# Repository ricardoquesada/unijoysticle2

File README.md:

# Unijoysticle™ 2

![logo][uni_logo]

Unijoysticle is a device that allows you to use modern Bluetooth gamepads and mice in retro computers.

Unijoysticle 2 models:

|                                          | 800XL                       | C64                         | A500                        | 2+                                 | 2                                     |
| ---------------------------------------- | --------------------------- | --------------------------- | --------------------------- | ---------------------------------- | ------------------------------------- |
| Top                                      | ![uni2800xl_photo_front]    | ![uni2c64_photo_front]      | ![uni2a500_photo_front]     | ![uni2plus_photo_front]            | ![uni2_photo_front]                   |
| Bottom                                   | ![uni2800xl_photo_back]     | ![uni2c64_photo_back]       | ![uni2a500_photo_back]      | ![uni2plus_photo_back]             | ![uni2_photo_back]                    |
| Release date                             | July 2023                   | March 2023                  | July 2022                   | October 2021                       | April 2019                            |
| Best for                                 | Atari 800XL / 600XL         | C64 / C128                  | Amiga                       | -                                  | -                                     |
| Good for                                 | Atari 400 / Amiga / AtariST | Amiga / AtariST             | C64 / AtariST / Atari 8bit  | C64 / Amiga / AtariST / Atari 8bit | C64 / Amiga / AtariST / Atari 8bit    |
| Status                                   | Active / Supported          | Active / Supported          | Active / Supported          | Discontinued / Supported           | Discontinued / Supported              |
| Amiga / AtariST mouse support            | Yes                         | No                          | Yes                         | Yes                                | Yes                                   |
| Amiga / AtariST 2nd & 3rd button support | No                          | No                          | Yes                         | Yes                                | Only in Port 1                        |
| Atari 8-bit 2nd & 3rd button support (5) | Yes                         | No                          | No                          | No                                 | No                                    |
| C64 2nd & 3rd button support             | No                          | Yes                         | No                          | No                                 | No                                    |
| C64 4th and 5th button support (4)       | No                          | Yes                         | No                          | No                                 | No                                    |
| C64 Paddle support                       | No                          | Might (1)                   | No                          | No                                 | No                                    |
| Rumble (2)                               | No                          | Yes                         | No                          | No                                 | No                                    |
| Fits                                     | 800XL / 600XL               | C64 / C128                  | Amiga 500 / 1200            | C64 / C128                         | C64 / C128                            |
| Buttons                                  | Reset, Mode, Swap           | Reset, Mode, Swap           | Reset, Mode,  Swap          | Reset, Mode                        | Reset, Mode                           |
| LEDs                                     | Port 1, 2, Bluetooth, Power | Port 1, 2, Bluetooth, Power | Port 1, 2, Bluetooth, Power | Port 1, 2, Power                   | Port 1, 2, Power                      |
| Filter noise ([Issue #17][issue_17])     | Yes                         | Yes                         | Yes                         | Yes                                | No                                    |
| Case friendly                            | Yes                         | Yes                         | Yes                         | Yes                                | No                                    |
| Easy to solder                           | No. Most components are SMD | No. Most components are SMD | No. Most components are SMD | No. Most components are SMD        | Yes. All components are through-hole  |
| Self-powered                             | Yes                         | Yes                         | Yes                         | Yes                                | Yes, can be turned on/off with switch |
| External power                           | USB                         | USB                         | USB                         | USB                                | Both USB and Barrel Jack 5V+          |
| Total Size (mm)                          | 65 x 75 x 13.6              | 72 x 68 x 13.6              | 67 x 72 x 13.6              | 64 x 64 x 13.6                     | 63 x 66 x 17                          |
| PCB Size (mm)                            | 53 x 72 x 1.6               | 63 x 60 x 1.6               | 52 x 67 x 1.6               | 49 x 62 x 1.6                      | 46 x 57 x 1.6                         |
| Weight (gr)                              | 27                          | 27.1                        | 25.6                        | 24                                 | 37                                    |
| Current (mA)                             | ~96                         | ~96                         | ~96                         | ~96                                | ~100                                  |
| USB connector                            | Micro USB                   | Micro USB                   | Micro USB                   | Micro USB                          | Micro USB                             |

Notes:

- (1): Hardware physically connected, but firmware is still WIP.
- (2): Some C64 games can turn on/off rumble on gamepads. See: [Rambo], and [Lemans] ([video][rumble_video])
- (3): Right and Middle mouse buttons not supported in C64.
- (4): Based on [CrystalCT 5 buttons joystick][crystalct/5plusbuttonsJoystick] ([video][5_buttons_video])
- (5): Based on [Ascrnet Joy 2B+][atari_joy2bplus]

Unijoysticle 2 allows you to use modern Bluetooth gamepads. E.g. DualSense controller in retro computers like the Commodore 64, Amiga and AtariST.

It also supports mice (for Amiga / AtariST only).

[issue_17]: https://gitlab.com/ricardoquesada/unijoysticle2/-/issues/17
[uni2_photo_front]: https://lh3.googleusercontent.com/pw/AM-JKLUphquTBg9JoV-L7wuMtze_aKIJ8LvfokTakuBKSVFClziLWCViggcrlNZtqGUMgv6u6yYpZ_RuE2jdGSn3Q0oYl0jOQzzGcutRt-JiMjLZY_oAvK4LehrawNj_aNbthCJ-VEJzsW3dywhJNekjhTsfNQ=-no
[uni2_photo_back]: https://lh3.googleusercontent.com/pw/AM-JKLXnMbJt7A55lUrtmiuKj4As98He7ZVi6YuPKg8N1sGbw1w5d5TtC8B-ilfoqC5QCKcZG8MFkmHNj5HgVbP8fdHhMBPx2CLgyRhaRmohx0SWF-_wZ57WYCfo7RlH4k7sEmh1txsTvHto2ko0H_0l9aUALg=-no
[uni2plus_photo_front]: https://lh3.googleusercontent.com/pw/AM-JKLWV2Zo912VtOfuM71AluanNXGwVQiAehNEiQ1VL3L7SkWDl-9k0fA6tfza9QpGL52petBfFFFHMb8rh_ybSj17LOQA70IycMDQw6AVqlN8Jp4HDWT8sWcXHIPEQZTxNuQ-RFygKbmVpW2n52wwi5cJgwA=-no
[uni2plus_photo_back]: https://lh3.googleusercontent.com/pw/AM-JKLWs_G63eJRX8WuVVRoKKur8UQ-VcWTNbmkjFumwZYvDRhgjqamVa-X9CROAnoPyK3sHDmfwtqAtJiI1DHiwlINBPCgiEY4yWFYWl8SlHA_QOG7LmVKuOKy1UQa-5dALC2r0FBfhS9He6utE7Kz5nWAXiw=-no
[uni2a500_photo_front]: https://lh3.googleusercontent.com/pw/AM-JKLU1BbKnbuLE7Oa_VOY3AnBjYwNVcAPKJcmYa7WUnCK5gMM1bHZyK3lTZ1Mo0NtS30ogeeSqxySx3Qi2ux3AGOlocQnQe9a87NoiKz5tnmHV_IGf3hPln0qsr8t5yfD5biKKVbGlRJ6vN2IbmI8H2Wg6iw=-no
[uni2a500_photo_back]: https://lh3.googleusercontent.com/pw/AM-JKLXMUngI6ctahY5clP-76UBjUem9L4Eehj4GFsEwUJwtZ3-MuZCV2nOsxiN3Go1PKvoc9sJbLRY8hCZ9TcV4cq5AtcAtscdjH1LiNzltFSgQY4IQEwSiPHfvhjhZCDezhgHKQDrmmA3EGFM7kJ4MKNxtig=-no
[bluepad32-fw]: https://gitlab.com/ricardoquesada/bluepad32
[uni2c64_photo_front]: https://lh3.googleusercontent.com/pw/AMWts8AzoDnIOIiM-50UpjAqY8OgdsM6pzM3BuYWb2ZOg4K_o4TxygtSjuZvrKI92lrl4Qqf8sLT6PtLYsXzDbragTDgoeX4yTpymqoc450FiyjiBT1YHxRbLBtGWgUOQHezXUxKCORs5aOcxPwowfrgR4PcQw=-no
[uni2c64_photo_back]: https://lh3.googleusercontent.com/pw/AMWts8C_vxauz3FAOv8NGAh64LGTExHwCj0N0bX73xsWIeDyR3efFPPUQb3JJQK5S8Qcm9B8bx3r_yio6WWAML1si4u8E9FejXP9DL8vxSCg_TR7rLi5aPiwisQaIptN8hJdfz3Zoh_B4cqiRE9vMi9t50R_gw=-no
[uni2800xl_photo_front]: https://lh3.googleusercontent.com/pw/AIL4fc9fcgdY3Gka6iSZmyUlBTA1Q9ABujo-9v_4qE85St2GdW-2TBzzLNx-pc25o0rFloL0ghWZDDVW_kGWpQjcXaP-SJf9NWPnNw-2jpc_8tcVKp8gzLH7fxnFd7DBEV1ahWYLy97WvthAy7p193wtZ7uM4w=-no
[uni2800xl_photo_back]: https://lh3.googleusercontent.com/pw/AIL4fc9PNSKKiA7PHsUTLKXGF1O9ywK-qLHS0nw2-Y6FxWQcgmtZJjajQh9Uch0aqZ2Pw-grH_Vg05IKYZilissF6nxUJPDszew0ouzGu91golm1RYJJpPS0CDANAfk3_O4qbwN_gam6dgGnafzsk4u0Xke0uw=-no
[Rambo]: https://gitlab.com/ricardoquesada/c64-rambo
[Lemans]: https://gitlab.com/ricardoquesada/c64-lemans
[crystalct/5plusbuttonsJoystick]: https://github.com/crystalct/5plusbuttonsJoystick/
[5_buttons_video]: https://www.youtube.com/watch?v=9Em_kUAHEuA
[rumble_video]: https://www.youtube.com/watch?v=vCj45OX43JE
[atari_joy2bplus]: https://github.com/ascrnet/Joy2Bplus
[uni_logo]: https://lh3.googleusercontent.com/pw/AIL4fc_k4CtBs9deXjMuCJOotXbNoRwON1CdYCMshG41PpEf2v-7xc2IcIPFvYCOFeLriESlXEJhm5nK72st8v1E04ZzyqawW8x5DPJt2ug6ZzhGXdnJvasD577CX1YbHRWDtmlz1JtyhDNHE_BeBeNnVb92vg=-w200-no?authuser=0

## Basic functionality

One Bluetooth gamepad controls one joystick.
You need two gamepads to control the two joysticks.

The mappings are:

- D-pad/joypad: controls up/down/left/right.
- Button A / Cross: fire button
- Button B / Circle: "up"  (ideal for platform games).
- Button X / Square: 2nd button (Amiga / AtariST only)
- Button Y / Triangle: 3rd button (Amiga / AtariST only)
- Button shoulder-right: autofire.
- System button swaps between Joystick 1 and 2

## Twin Stick functionality (AKA Enhanced mode)

When in "Enhanced mode", you control the two joysticks with only one gamepad.
The mappings are:

- Left joypad / d-pad: control Joystick 2 movements.
- Right joypad: control Joystick 1 movements.
- Button A / Cross: fire for Joystick 2
- Button B / Circle: fire for Joystick 1
- Button X / Square: 2nd button for Joystick 2
- Button Y / Triangle: 2nd button for Joystick 1
- Button Shoulder Left: auto-fire for Joystick 2
- Button Shoulder Right: auto-fire for Joystick 1

This mode is ideal for games like [Commando][2] or [1942][3] since it allows you
throw grenades / roll by pressing Button B.

## Supported controllers

### Gamepads

- Sony DualSense
- Sony DUALSHOCK 4
- Sony DUALSHOCK 3
- Nintendo Switch Pro
- Nintendo JoyCons
- Nintendo Wii U
- Nintendo Wii + accesories
- Xbox Wireless controller (model 1708)
- Steam
- Stadia
- Android gamepads
- PC/Windows gamepads
- 8BitDo controllers
- iCade
- And more

See:

* [Supported gamepads][gamepads]
* [Supported mice][mice]

[gamepads]: https://gitlab.com/ricardoquesada/unijoysticle2/blob/master/docs/supported_gamepads.md
[mice]: https://gitlab.com/ricardoquesada/bluepad32/blob/develop/docs/supported_mice.md

### Mice

Mouse emulation is only available for **Amiga and Atari ST** computers.

For a detailed list of supported mice, see here:

* [Supported mice][supported_mice]

[supported_mice]:  https://gitlab.com/ricardoquesada/bluepad32/blob/develop/docs/supported_mice.md

## Order info

If you are looking for ready-to-use boards, you can purchase one from here:

Looking for a remix and/or 3rd party vendors. Go here: [SELLING_DEVICES.md][selling_devices]

[selling_devices]: SELLING_DEVICES.md

## More Info

- [Users guide][users_guide]
- [Discord][discord]
- [Email group][email_group]

[users_guide]: https://gitlab.com/ricardoquesada/unijoysticle2/blob/master/docs/user_guide.md
[discord]: https://discord.gg/r5aMn6Cw5q
[email_group]: https://groups.google.com/forum/#!forum/unijoysticle

[1]: https://retro.moe/unijoysticle
[2]: https://csdb.dk/release/?id=137173
[3]: https://csdb.dk/release/?id=38140

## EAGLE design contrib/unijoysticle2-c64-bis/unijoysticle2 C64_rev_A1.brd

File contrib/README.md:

Contributions by the community.

Kopsec C64:
 - c64/ Unijoysticle 2 - REV E / REV H
 - c64/ Unijoysticle 2 - Rev A1, based on new Unijoysticle C64 model

Eduardo Casino:
 - C16/Plus4 board

Hyvax:
  - NeoGeo board

Aakko:
  - Case for Unijosyticle 2+

Goblin Hero:
  - Case for Unijoysticle 2 A500

Albert Herranz:
  - MSX boards
    * [msx-joyblue-v1](https://github.com/herraa1/msx-joyblue-v1)
    * [msx-joyblue-v2](https://github.com/herraa1/msx-joyblue-v2)

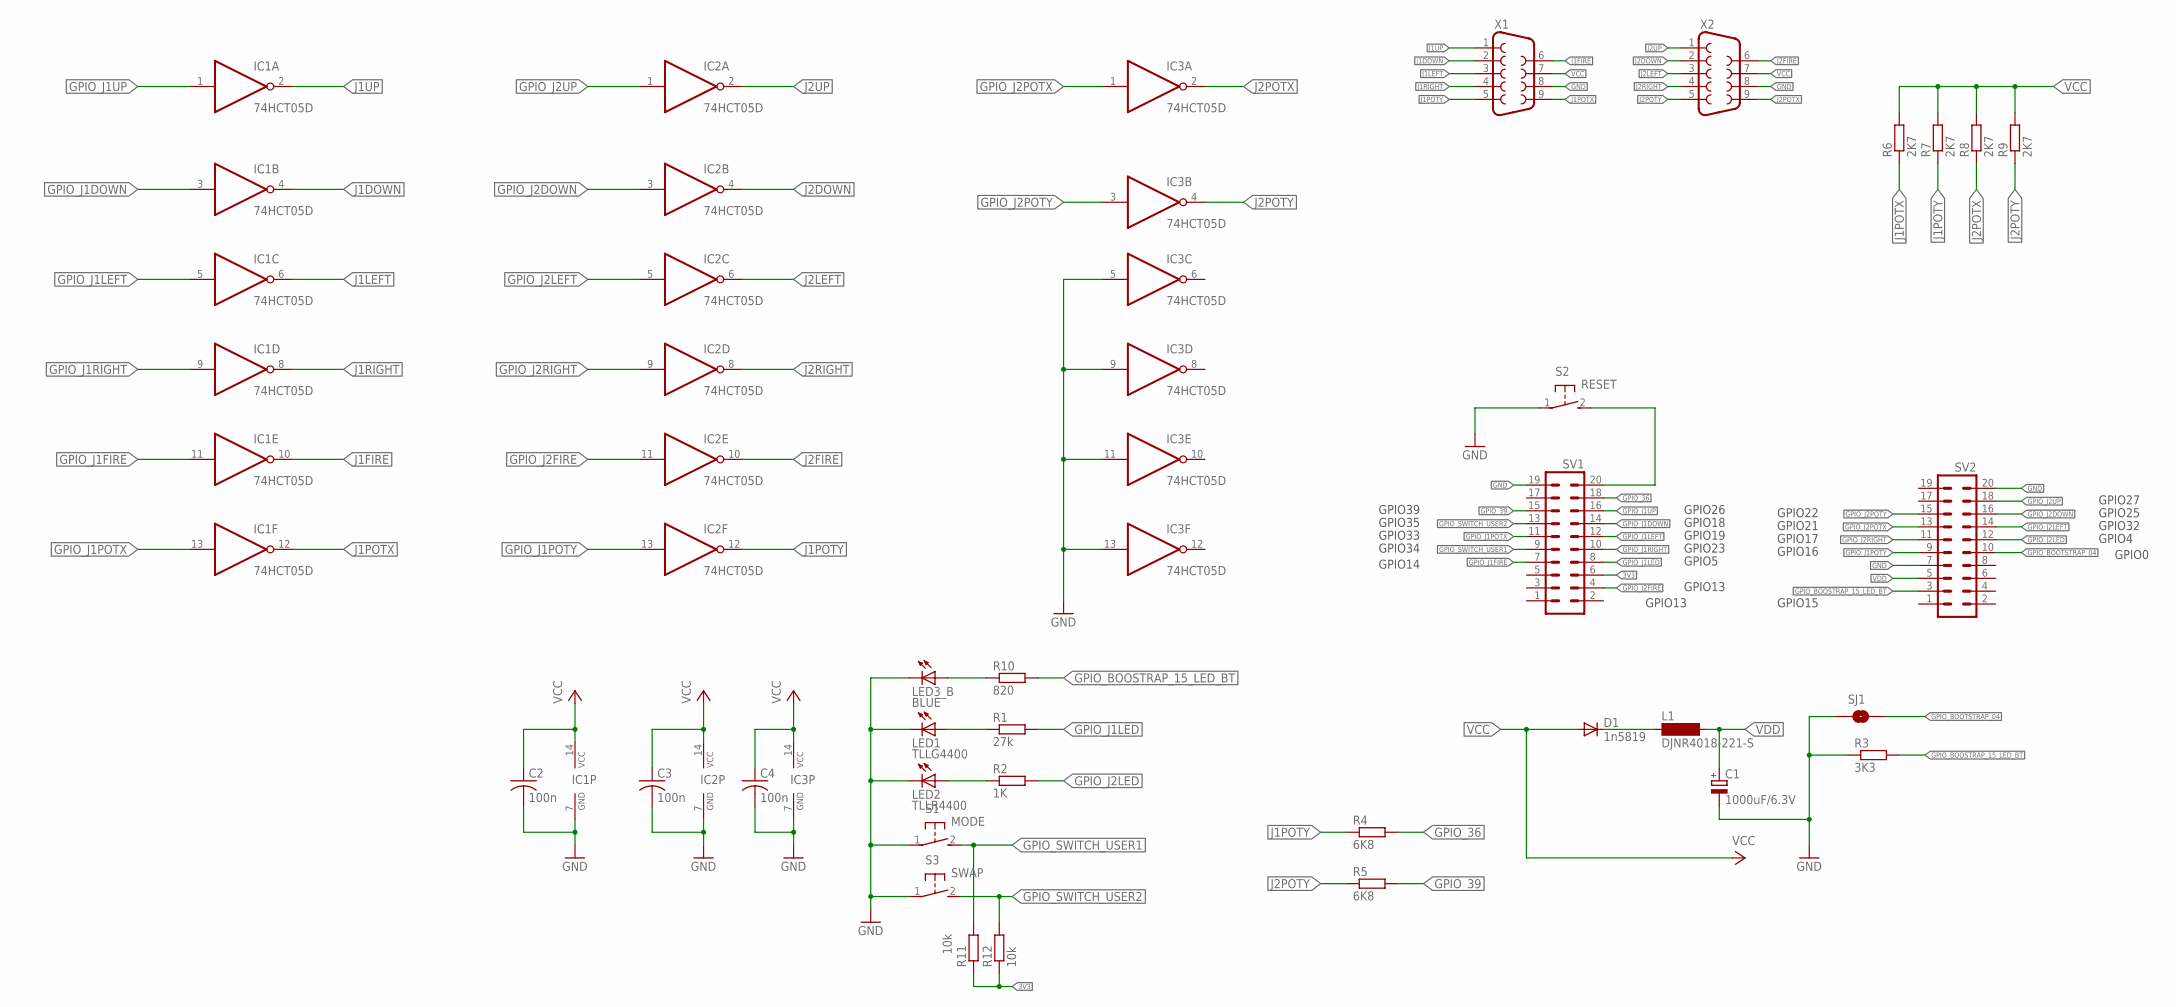
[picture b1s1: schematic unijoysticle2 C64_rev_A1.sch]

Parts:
C1: 1000uF/6.3V; 140CLH-1010
C2, C3, C4: 100n; C0805K
D1: 1n5819; DO214AC
IC1, IC2, IC3: 74HCT05D; SO14
L1: DJNR4018-221-S; SM-NE45
LED1: TLLG4400; LED3MM
LED2: TLLR4400; LED3MM
LED3_B: BLUE; LED3MM
R1: 27k; M0805
R2: 1K; M0805
R3: 3K3; M0805
R4, R5: 6K8; M0805
R6, R7, R8, R9: 2K7; M0805
R10: 820; M0805
R11, R12: 10k; M0805
S1: MODE; B3F-31XX
S2: RESET; B3F-31XX
S3: SWAP; B3F-31XX
SJ1: SOLDERJUMPERTRACE; SJ_2S-TRACE
SV1, SV2: MA10-2
X1, X2: DB9

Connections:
3V3: R11.1, R12.1, SV1.6
GND: C1.-, C2.2, C3.2, C4.2, IC1.7 (GND), IC2.7 (GND), IC3.5 (I), IC3.7 (GND), IC3.9 (I), IC3.11 (I), IC3.13 (I), LED1.K (C), LED2.K (C), LED3_B.K (C), R3.1, S1.1, S2.1, S3.1, SJ1.1, SV1.19, SV2.7, SV2.20, X1.8, X2.8
GPIO_36: R4.2, SV1.18
GPIO_39: R5.2, SV1.15
GPIO_BOOSTRAP_15_LED_BT: R3.2, R10.2, SV2.3
GPIO_BOOTSTRAP_04: SJ1.2, SV2.10
GPIO_J1DOWN: IC1.3 (I), SV1.14
GPIO_J1FIRE: IC1.11 (I), SV1.7
GPIO_J1LED: R1.2, SV1.8
GPIO_J1LEFT: IC1.5 (I), SV1.12
GPIO_J1POTX: IC1.13 (I), SV1.11
GPIO_J1POTY: IC2.13 (I), SV2.9
GPIO_J1RIGHT: IC1.9 (I), SV1.10
GPIO_J1UP: IC1.1 (I), SV1.16
GPIO_J2DOWN: IC2.3 (I), SV2.16
GPIO_J2FIRE: IC2.11 (I), SV1.4
GPIO_J2LED: R2.2, SV2.12
GPIO_J2LEFT: IC2.5 (I), SV2.14
GPIO_J2POTX: IC3.1 (I), SV2.13
GPIO_J2POTY: IC3.3 (I), SV2.15
GPIO_J2RIGHT: IC2.9 (I), SV2.11
GPIO_J2UP: IC2.1 (I), SV2.18
GPIO_SWITCH_USER1: R11.2, S1.2 (S), SV1.9
GPIO_SWITCH_USER2: R12.2, S3.2 (S), SV1.13
J1DOWN: IC1.4 (O), X1.2
J1FIRE: IC1.10 (O), X1.6
J1LEFT: IC1.6 (O), X1.3
J1POTX: IC1.12 (O), R6.1, X1.9
J1POTY: IC2.12 (O), R4.1, R7.1, X1.5
J1RIGHT: IC1.8 (O), X1.4
J1UP: IC1.2 (O), X1.1
J2DOWN: IC2.4 (O), X2.2
J2FIRE: IC2.10 (O), X2.6
J2LEFT: IC2.6 (O), X2.3
J2POTX: IC3.2 (O), R8.1, X2.9
J2POTY: IC3.4 (O), R5.1, R9.1, X2.5
J2RIGHT: IC2.8 (O), X2.4
J2UP: IC2.2 (O), X2.1
unnamed: LED1.A, R1.1
unnamed: LED2.A, R2.1
unnamed: S2.2 (S), SV1.20
unnamed: LED3_B.A, R10.1
unnamed: D1.C, L1.1
VCC: C2.1, C3.1, C4.1, D1.A, IC1.14 (VCC), IC2.14 (VCC), IC3.14 (VCC), R6.2, R7.2, R8.2, R9.2, X1.7, X2.7
VDD: C1.+, L1.2, SV2.5

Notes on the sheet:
GPIO35
GPIO33
GPIO34
GPIO14
GPIO39
GPIO26
GPIO18
GPIO19
GPIO23
GPIO5
GPIO13
GPIO27
GPIO25
GPIO32
GPIO4
GPIO0
GPIO22
GPIO21
GPIO17
GPIO16
GPIO15

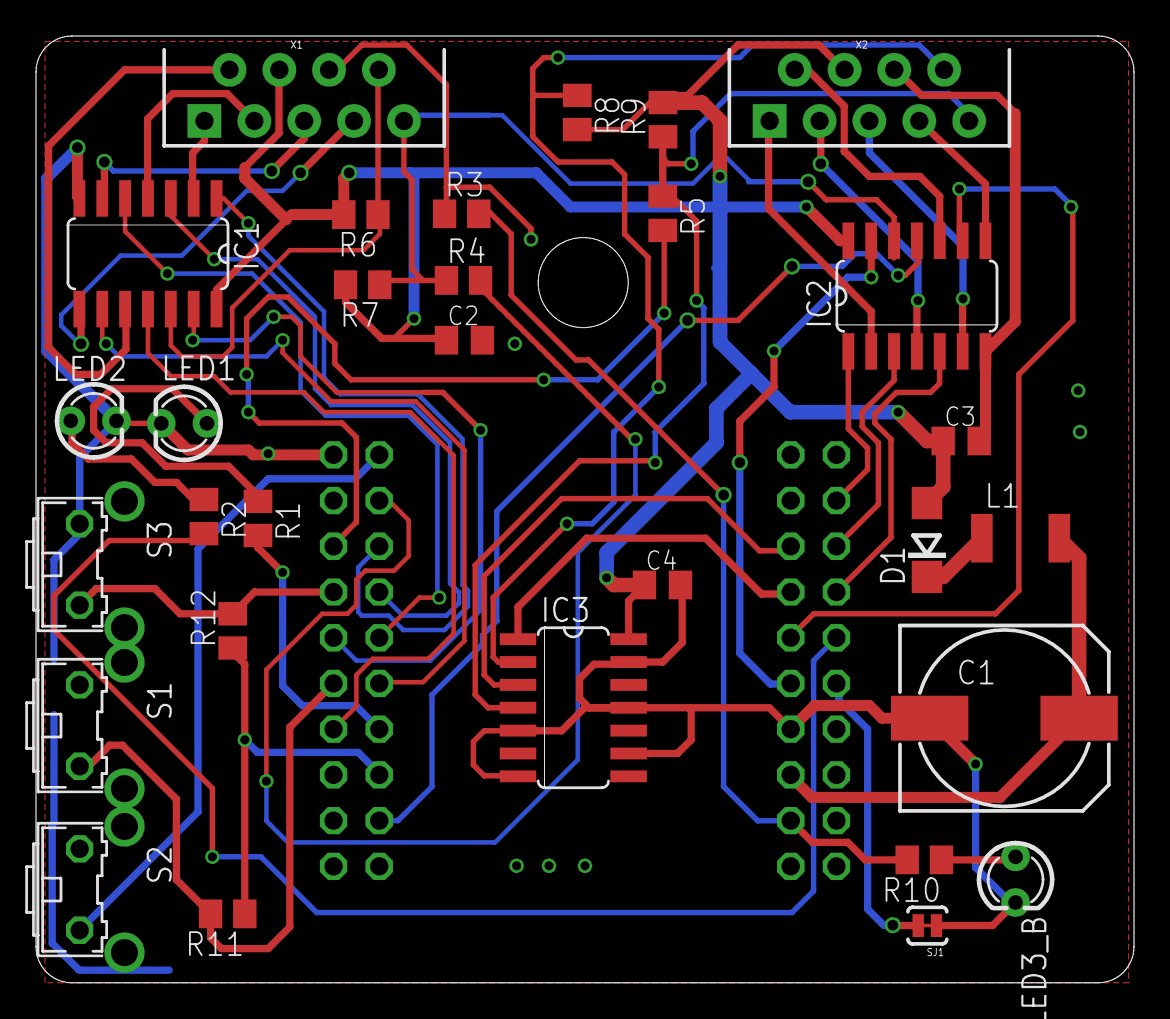
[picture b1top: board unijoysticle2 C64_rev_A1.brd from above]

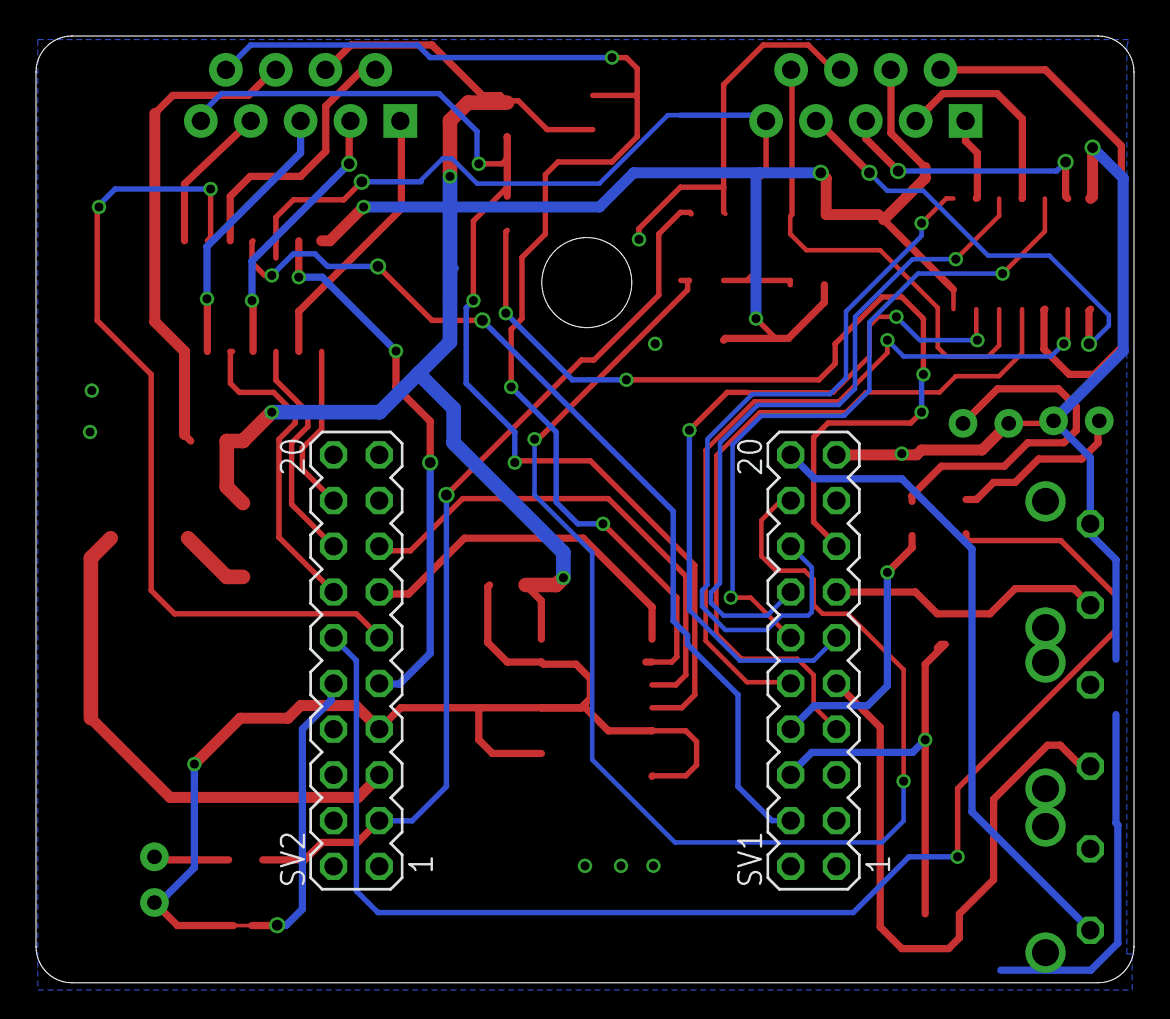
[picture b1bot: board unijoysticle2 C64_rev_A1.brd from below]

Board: 2 copper layers, 61.0 x 52.6 mm, 32 parts (2 on the bottom side), 45 nets.

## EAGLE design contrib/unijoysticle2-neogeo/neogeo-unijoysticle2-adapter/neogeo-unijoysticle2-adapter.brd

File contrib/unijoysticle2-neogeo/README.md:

# Unijoysticle2 for NeoGeo

## Projects

### Unijoysticle2 for NeoGeo

Includes PCB & schematic (Eagle CAD 6.5.0): Unijoysticle2 NeoGeo version - with DB15 connector.

### Unijoysticle2 Adapter for NeoGeo

Includes PCB & schematic (Eagle CAD 6.5.0): Adapter for Unijoysticle2 - 2x DB9 -> DB15

## NeoGeo pinout

- NeoGeo DB15 pinout reference
- C64 control port pinout reference
- table describing how corresponding pins are connected
- gamepad button mappings, NeoGeo and MVS controller for reference

## Mappings

Replace file `uni_joystick.c` in in Bluepad32 source code and compile it using `unijoysticle` as `PLATFORM`.

## Additional notes

- neogeo-unijoysticle2 is supposed to be ONLY used as self powered - do not plug in usb power simultaneously, there are no protection diodes (add em if You wish)
- before exporting to gerber all traces on board files should be further optimized, can be traced better/prettier
- description layers should be cleaned up and aligned
- board dimensions should be further adjusted
- uni_joystick.c is still from the version before "enhanced mode bug fix" so J2 = J1
- ment to be used in enhanced mode only, of course, due to 10 controller inputs are required - there is no point in using it in basic mode
- tested 11.12.2021 and working fine with NeoGeo MVS MV1A - should of course work as well with other MVS boards and AES
- keep in mind some MVS supergun's may have DB15 connectors upside down - mirror DB15 connector on the adapter or standalone pcb before making gerbers, otherwise (due to esp32 sticking up out of the pcb) there may be issues plugging in adapter or standalone pcb to Your MVS or AES
- solder cup DB15/DB9 connector or THT connectors may be used - alter board files according to Your preferences

## Author

Hyvax

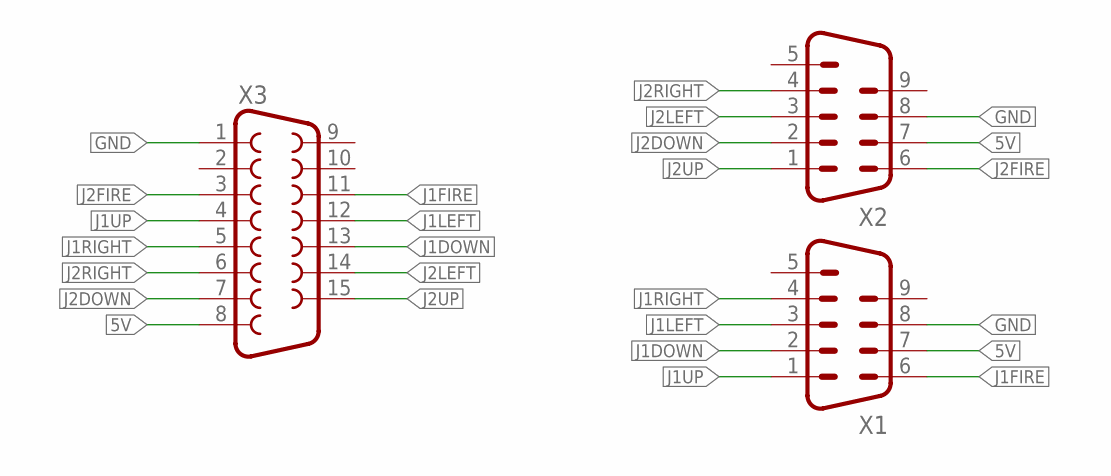
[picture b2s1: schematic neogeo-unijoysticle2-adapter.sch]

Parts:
X1, X2: M09D
X3: F15D

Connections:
5V: X1.7, X2.7, X3.8
GND: X1.8, X2.8, X3.1
J1DOWN: X1.2, X3.13
J1FIRE: X1.6, X3.11
J1LEFT: X1.3, X3.12
J1RIGHT: X1.4, X3.5
J1UP: X1.1, X3.4
J2DOWN: X2.2, X3.7
J2FIRE: X2.6, X3.3
J2LEFT: X2.3, X3.14
J2RIGHT: X2.4, X3.6
J2UP: X2.1, X3.15

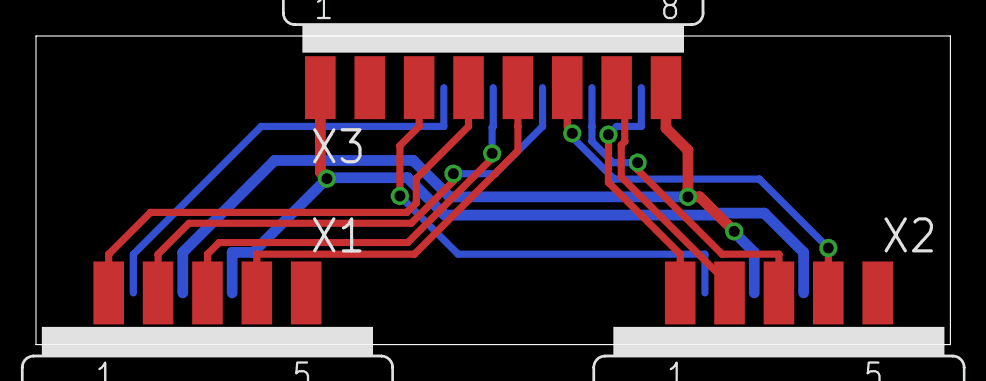
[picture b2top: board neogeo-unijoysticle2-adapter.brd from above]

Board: 2 copper layers, 50.8 x 17.1 mm, 3 parts (0 on the bottom side), 12 nets.

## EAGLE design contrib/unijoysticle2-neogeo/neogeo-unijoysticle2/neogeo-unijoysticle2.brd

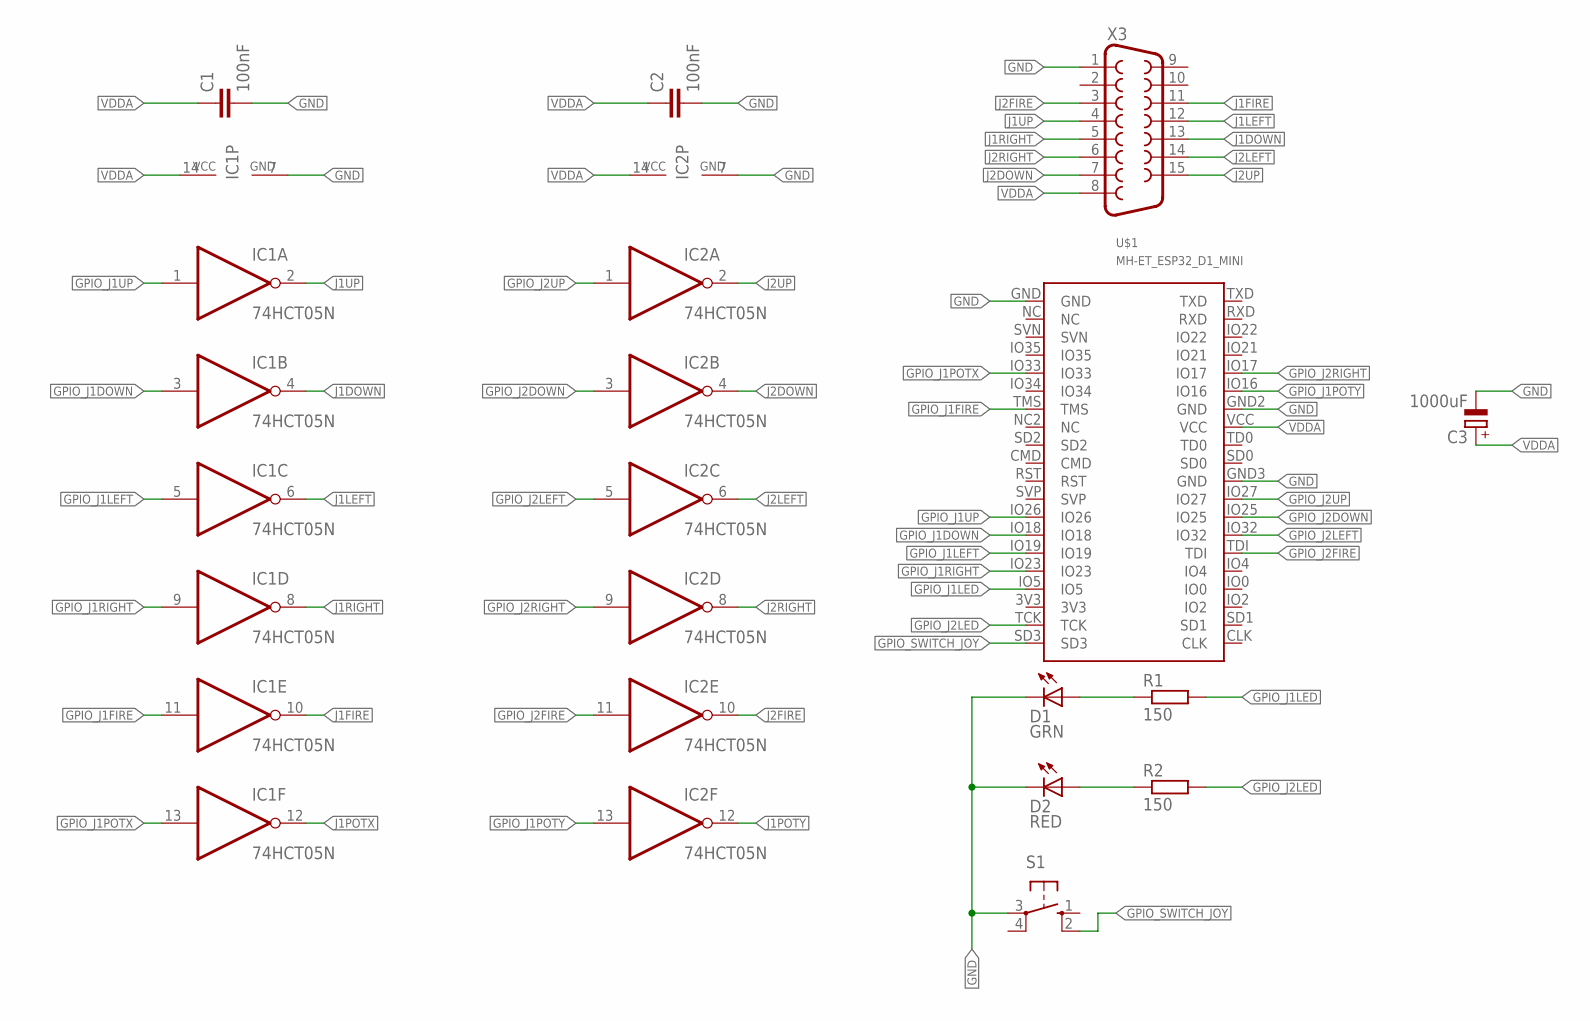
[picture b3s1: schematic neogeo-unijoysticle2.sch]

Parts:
C1, C2: 100nF; C025-025X050
C3: 1000uF; E2,5-6E
D1: GRN; LED3MM
D2: RED; LED3MM
IC1, IC2: 74HCT05N; DIL14
R1, R2: 150; 0207/7
S1: 10-XX; B3F-10XX
U$1: MH-ET_ESP32_D1_MINI
X3: F15HP

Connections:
GND: C1.2, C2.2, C3.-, D1.K (C), D2.K (C), IC1.7 (GND), IC2.7 (GND), S1.3, U$1.GND, U$1.GND2 (GND), U$1.GND3 (GND), X3.1
GPIO_J1DOWN: IC1.3 (I), U$1.IO18
GPIO_J1FIRE: IC1.11 (I), U$1.TMS
GPIO_J1LED: R1.2, U$1.IO5
GPIO_J1LEFT: IC1.5 (I), U$1.IO19
GPIO_J1POTX: IC1.13 (I), U$1.IO33
GPIO_J1POTY: IC2.13 (I), U$1.IO16
GPIO_J1RIGHT: IC1.9 (I), U$1.IO23
GPIO_J1UP: IC1.1 (I), U$1.IO26
GPIO_J2DOWN: IC2.3 (I), U$1.IO25
GPIO_J2FIRE: IC2.11 (I), U$1.TDI
GPIO_J2LED: R2.2, U$1.TCK
GPIO_J2LEFT: IC2.5 (I), U$1.IO32
GPIO_J2RIGHT: IC2.9 (I), U$1.IO17
GPIO_J2UP: IC2.1 (I), U$1.IO27
GPIO_SWITCH_JOY: S1.2 (S1), U$1.SD3
J1DOWN: IC1.4 (O), X3.13
J1FIRE: IC1.10 (O), X3.11
J1LEFT: IC1.6 (O), X3.12
J1POTX: IC1.12 (O)
J1POTY: IC2.12 (O)
J1RIGHT: IC1.8 (O), X3.5
J1UP: IC1.2 (O), X3.4
J2DOWN: IC2.4 (O), X3.7
J2FIRE: IC2.10 (O), X3.3
J2LEFT: IC2.6 (O), X3.14
J2RIGHT: IC2.8 (O), X3.6
J2UP: IC2.2 (O), X3.15
unnamed: D1.A, R1.1
unnamed: D2.A, R2.1
VDDA: C1.1, C2.1, C3.+, IC1.14 (VCC), IC2.14 (VCC), U$1.VCC, X3.8

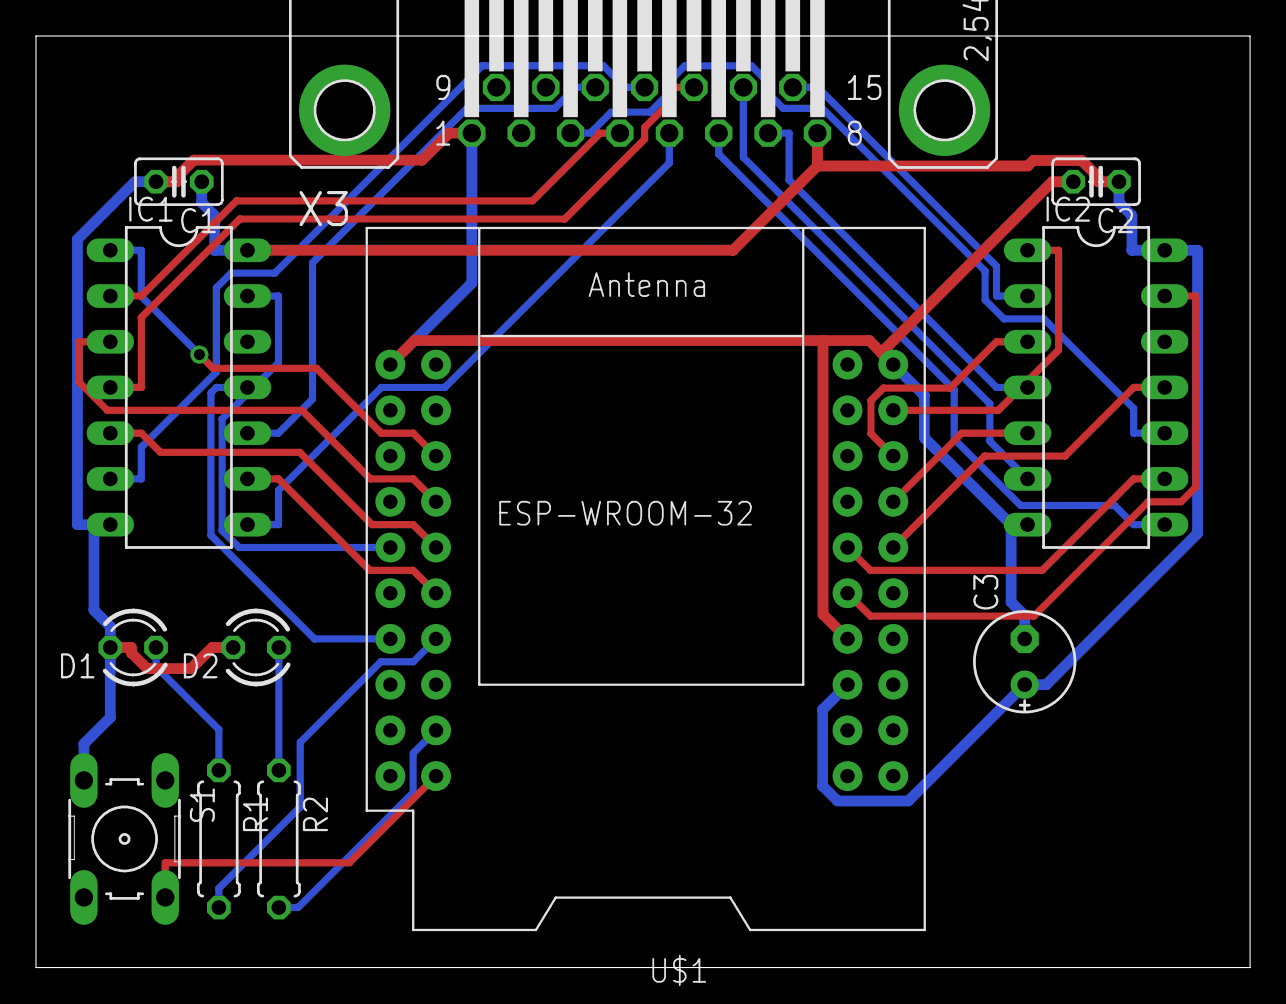
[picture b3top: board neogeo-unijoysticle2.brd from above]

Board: 2 copper layers, 67.4 x 51.8 mm, 12 parts (0 on the bottom side), 29 nets.

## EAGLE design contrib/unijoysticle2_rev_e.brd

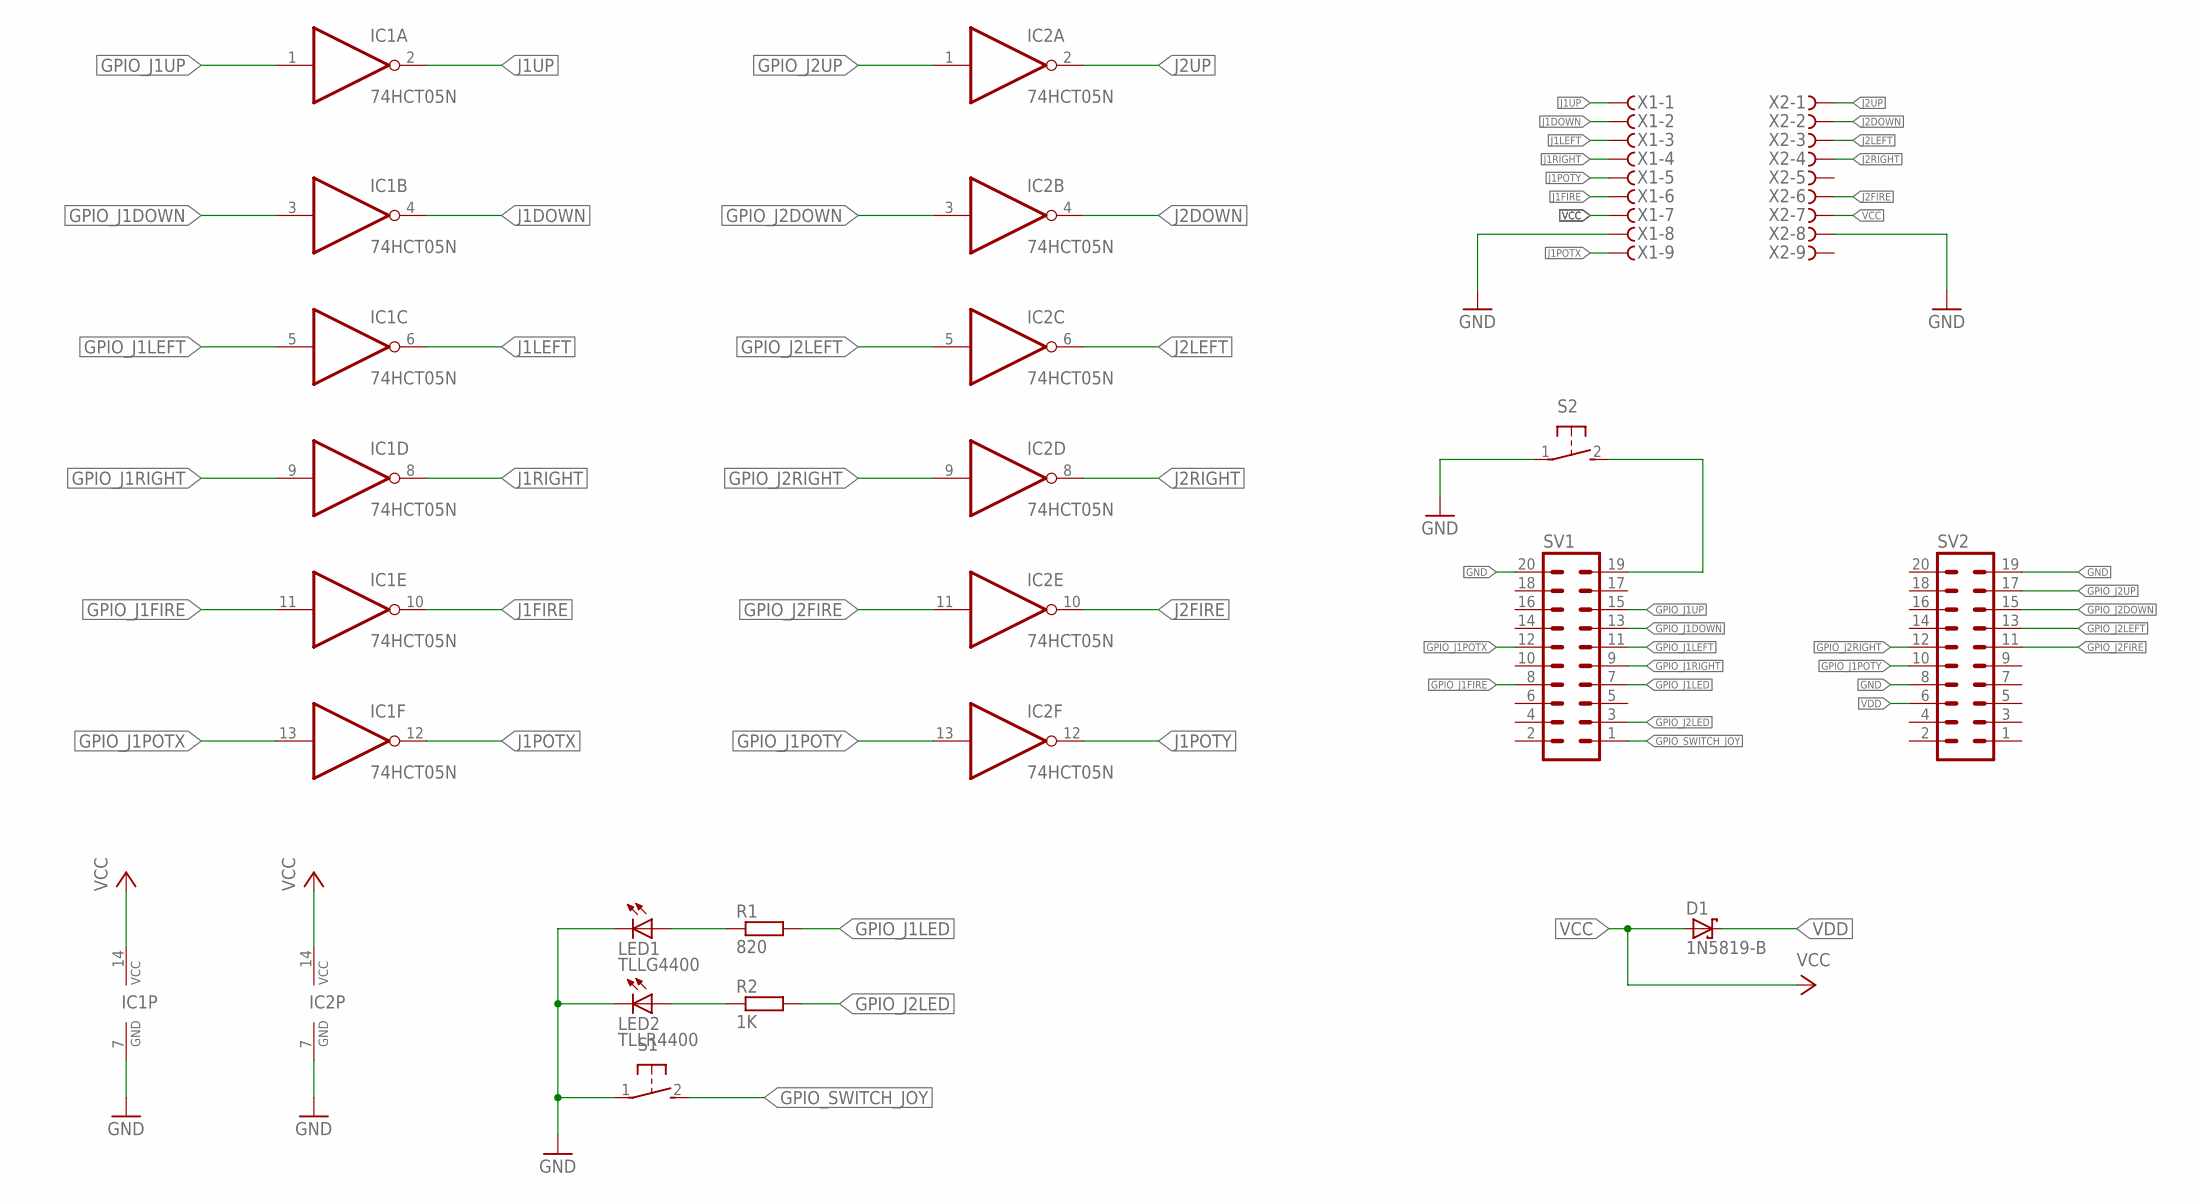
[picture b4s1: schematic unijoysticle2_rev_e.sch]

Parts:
D1: 1N5819-B; DO41-7.6
IC1, IC2: 74HCT05N; DIL14
LED1: TLLG4400; LED3MM
LED2: TLLR4400; LED3MM
R1: 820; 0309/10
R2: 1K; 0309/10
S1, S2: 31-XX; B3F-31XX
SV1, SV2: MA10-2
X1, X2: F09DS; F09D

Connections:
GND: IC1.7 (GND), IC2.7 (GND), LED1.K (C), LED2.K (C), S1.1, S2.1, SV1.20, SV2.8, SV2.19, X1.8, X2.8
GPIO_J1DOWN: IC1.3 (I), SV1.13
GPIO_J1FIRE: IC1.11 (I), SV1.8
GPIO_J1LED: R1.2, SV1.7
GPIO_J1LEFT: IC1.5 (I), SV1.11
GPIO_J1POTX: IC1.13 (I), SV1.12
GPIO_J1POTY: IC2.13 (I), SV2.10
GPIO_J1RIGHT: IC1.9 (I), SV1.9
GPIO_J1UP: IC1.1 (I), SV1.15
GPIO_J2DOWN: IC2.3 (I), SV2.15
GPIO_J2FIRE: IC2.11 (I), SV2.11
GPIO_J2LED: R2.2, SV1.3
GPIO_J2LEFT: IC2.5 (I), SV2.13
GPIO_J2RIGHT: IC2.9 (I), SV2.12
GPIO_J2UP: IC2.1 (I), SV2.17
GPIO_SWITCH_JOY: S1.2 (S), SV1.1
J1DOWN: IC1.4 (O), X1.2
J1FIRE: IC1.10 (O), X1.6
J1LEFT: IC1.6 (O), X1.3
J1POTX: IC1.12 (O), X1.9
J1POTY: IC2.12 (O), X1.5
J1RIGHT: IC1.8 (O), X1.4
J1UP: IC1.2 (O), X1.1
J2DOWN: IC2.4 (O), X2.2
J2FIRE: IC2.10 (O), X2.6
J2LEFT: IC2.6 (O), X2.3
J2RIGHT: IC2.8 (O), X2.4
J2UP: IC2.2 (O), X2.1
unnamed: LED1.A, R1.1
unnamed: LED2.A, R2.1
unnamed: S2.2 (S), SV1.19
VCC: D1.A, IC1.14 (VCC), IC2.14 (VCC), X1.7, X2.7
VDD: D1.C, SV2.6

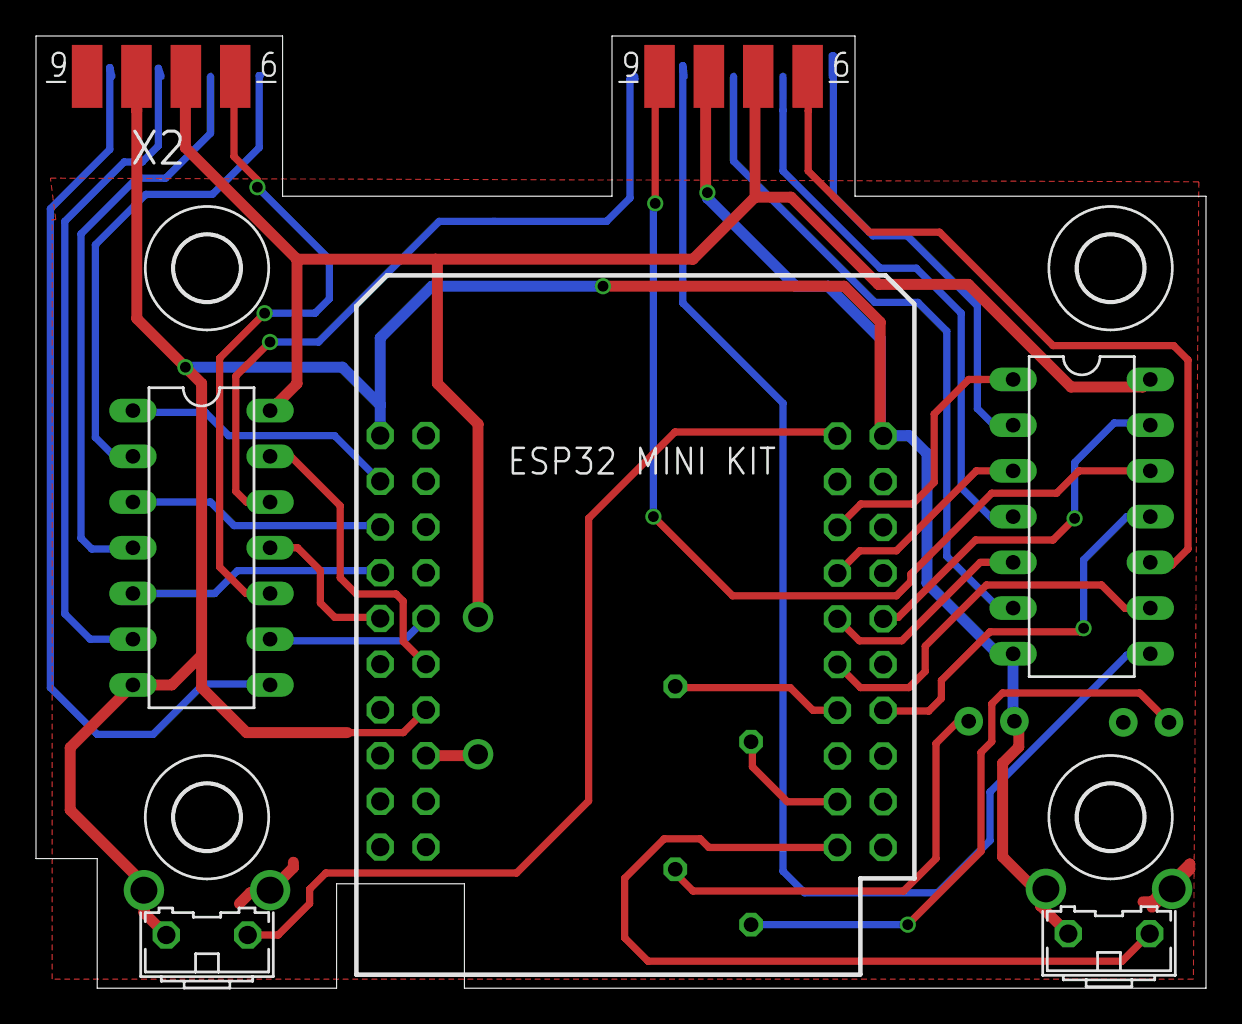
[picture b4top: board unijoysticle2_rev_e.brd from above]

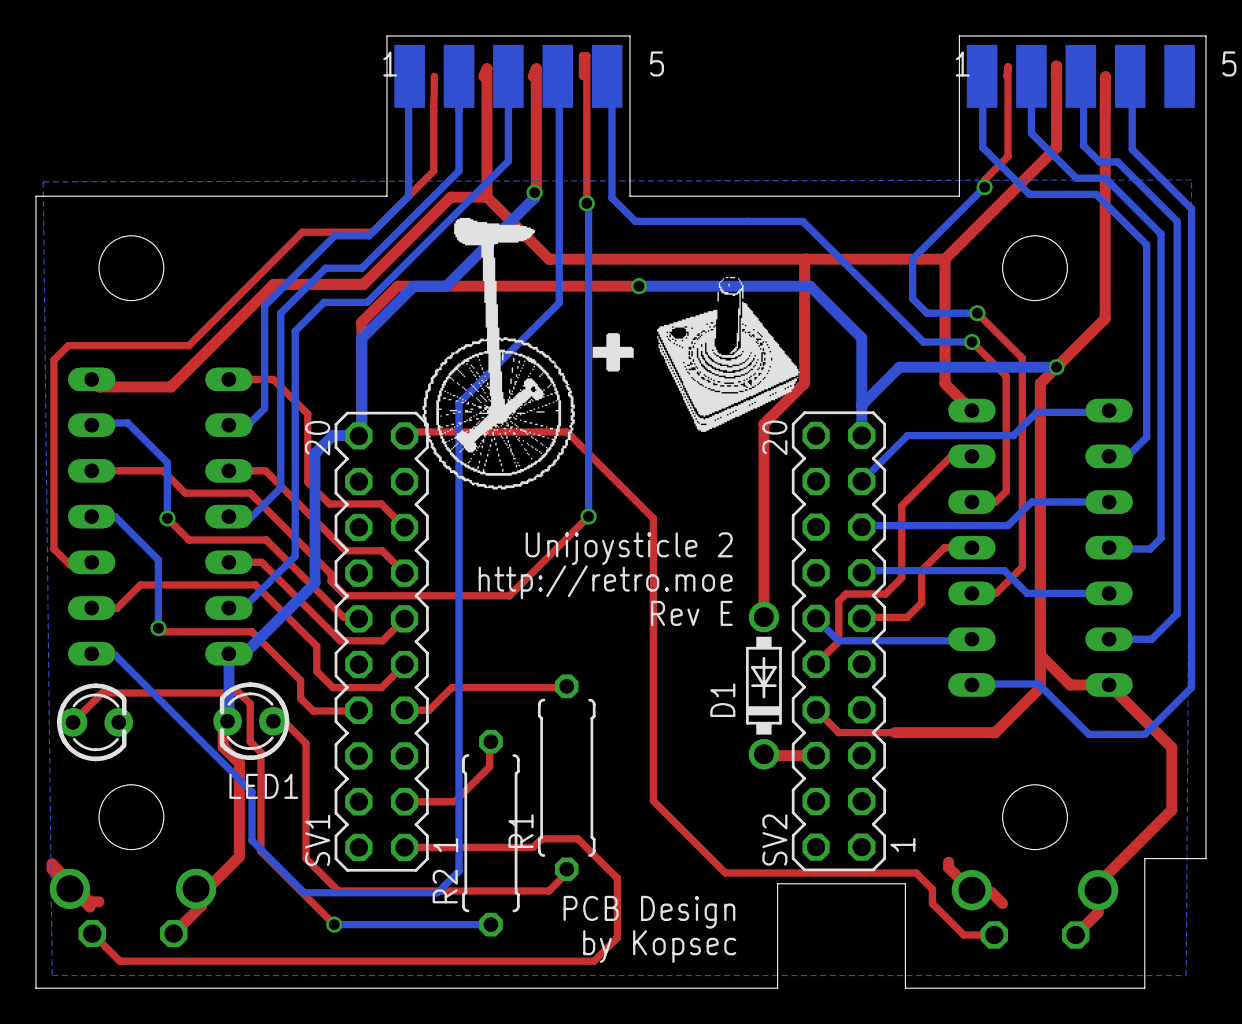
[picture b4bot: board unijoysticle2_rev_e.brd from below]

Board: 2 copper layers, 65.0 x 52.9 mm, 18 parts (9 on the bottom side), 33 nets.

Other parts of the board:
U$1, U$2, U$3, U$4: 3,6
U$5: OSHW_5MM

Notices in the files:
parts and their libraries:
SparkFun mod mini din 7: Licensing: CC v3.0 Share-Alike You are welcome to use this library for commercial purposes.
